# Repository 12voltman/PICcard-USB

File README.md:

# PICcard-USB
Small PIC development board for high resistive switching (à-la Makey Makey)

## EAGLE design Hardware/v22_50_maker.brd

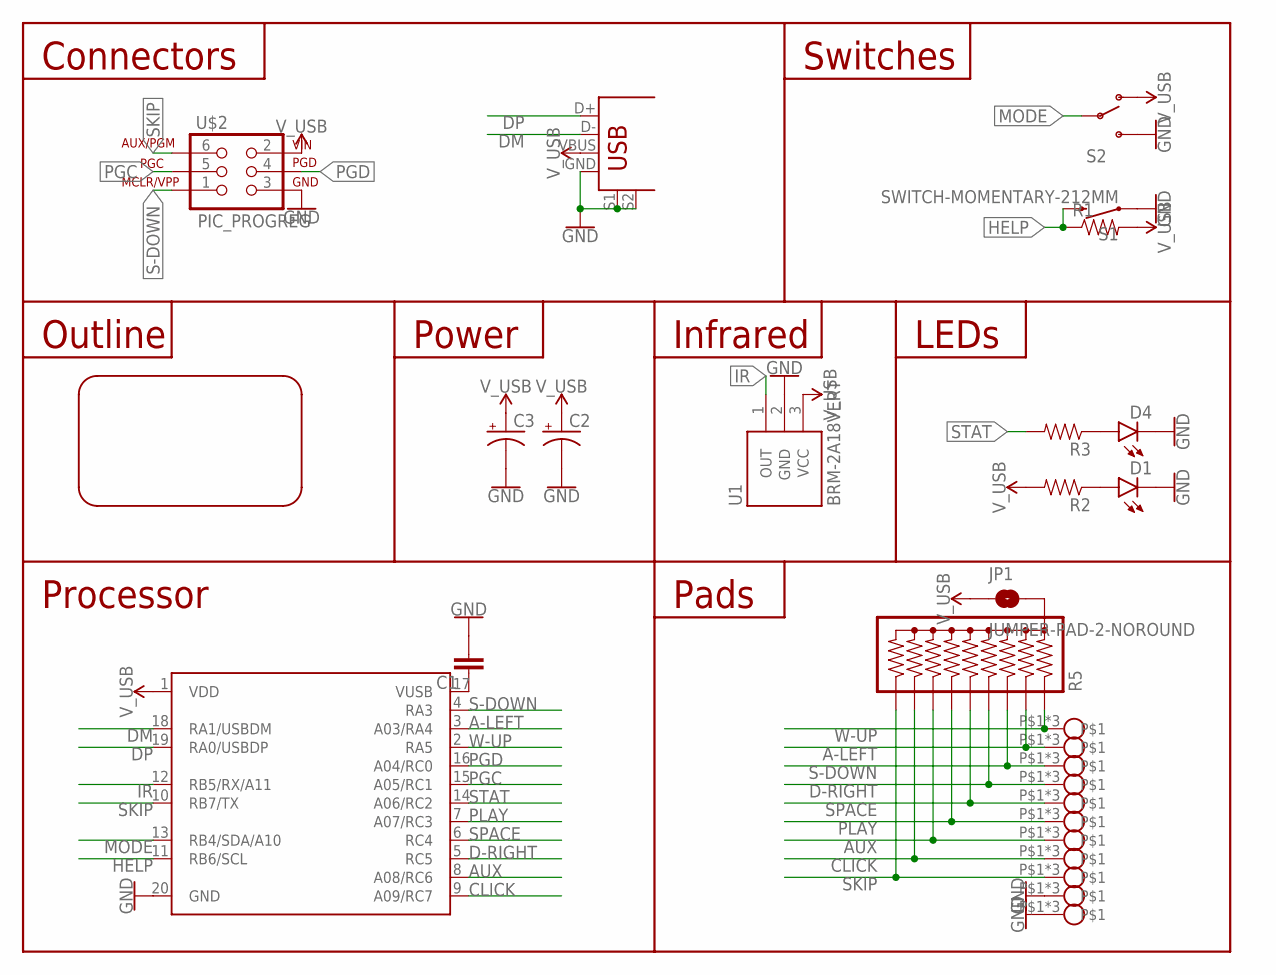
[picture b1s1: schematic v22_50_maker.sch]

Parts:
C1: CAPPTH; CAP-PTH-SMALL
C2: CAP_POLPTH2; CPOL-RADIAL-10UF-25V
C3: CAP_POLPTH1; CPOL-RADIAL-100UF-25V
D1, D4: LED3MM
JP1: JUMPER-PAD-2-NOROUND; PAD-JUMPER-2-NO_YES_SILK_ROUND
R1, R2, R3: RESISTORAXIAL-0.3; AXIAL-0.3
R5: RPACK-BUSSED-9ROUND; RPACK-SIP-PTH-9
S1: SWITCH-MOMENTARY-212MM; TACTILE-PTH-12MM
S2: SWITCH-SPDTPTH; SWITCH-SPDT
U1: BRM-2A18VERT; BRM-2508_VERT
U$1: PIC16F1459-I/MLDIL; DIL20
U$2: PIC_PROGREG; 1X06
U$3: USB+SHIELD; USB-B-PTH
U$4, U$5, U$6, U$7, U$8, U$9, U$10, U$11, U$12, U$13, U$14: ALLIGATOR; ALLIGATOR_CLIP_CONNECTOR
U$15: CARD_STANDARD50MM; IEC-7810_ID-1_50MM

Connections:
A-LEFT: R5.P$3 (3), U$1.3 (A03/RA4), U$4.P$1, U$4.P$2, U$4.P$3
AUX: R5.P$8 (8), U$1.8 (A08/RC6), U$10.P$1, U$10.P$2, U$10.P$3
CLICK: R5.P$9 (9), U$1.9 (A09/RC7), U$11.P$1, U$11.P$2, U$11.P$3
D-RIGHT: R5.P$5 (5), U$1.5 (RC5), U$5.P$1, U$5.P$2, U$5.P$3
DM: U$1.18 (RA1/USBDM), U$3.D-
DP: U$1.19 (RA0/USBDP), U$3.D+
GND: C1.2, C2.2 (-), C3.2 (-), D1.K (C), D4.K (C), S1.1, S1.2 (1), S2.3 (S), U1.2 (GND), U$1.20 (GND), U$2.3 (GND), U$3.GND, U$3.S1, U$3.S2, U$13.P$1, U$13.P$2, U$13.P$3, U$14.P$1, U$14.P$2, U$14.P$3
HELP: R1.P$1 (1), S1.3 (2), S1.4 (2), U$1.11 (RB6/SCL)
IR: U1.1 (OUT), U$1.12 (RB5/RX/A11)
MODE: S2.2, U$1.13 (RB4/SDA/A10)
unnamed: D4.A, R3.P$1 (1)
unnamed: C1.1, U$1.17 (VUSB)
unnamed: JP1.2, R5.P$1 (1)
unnamed: D1.A, R2.P$1 (1)
PGC: U$1.15 (A05/RC1), U$2.5 (PGC)
PGD: U$1.16 (A04/RC0), U$2.4 (PGD)
PLAY: R5.P$7 (7), U$1.7 (A07/RC3), U$9.P$1, U$9.P$2, U$9.P$3
S-DOWN: R5.P$4 (4), U$1.4 (RA3), U$2.1 (MCLR/VPP), U$7.P$1, U$7.P$2, U$7.P$3
SKIP: R5.P$10 (10), U$1.10 (RB7/TX), U$2.6 (AUX/PGM), U$12.P$1, U$12.P$2, U$12.P$3
SPACE: R5.P$6 (6), U$1.6 (RC4), U$8.P$1, U$8.P$2, U$8.P$3
STAT: R3.P$2 (2), U$1.14 (A06/RC2)
V_USB: C2.1 (+), C3.1 (+), JP1.1, R1.P$2 (2), R2.P$2 (2), S2.1 (O), U1.3 (VCC), U$1.1 (VDD), U$2.2 (VIN), U$3.VBUS
W-UP: R5.P$2 (2), U$1.2 (RA5), U$6.P$1, U$6.P$2, U$6.P$3

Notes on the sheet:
Switches
Connectors
Outline
Power
Infrared
LEDs
Pads
Processor

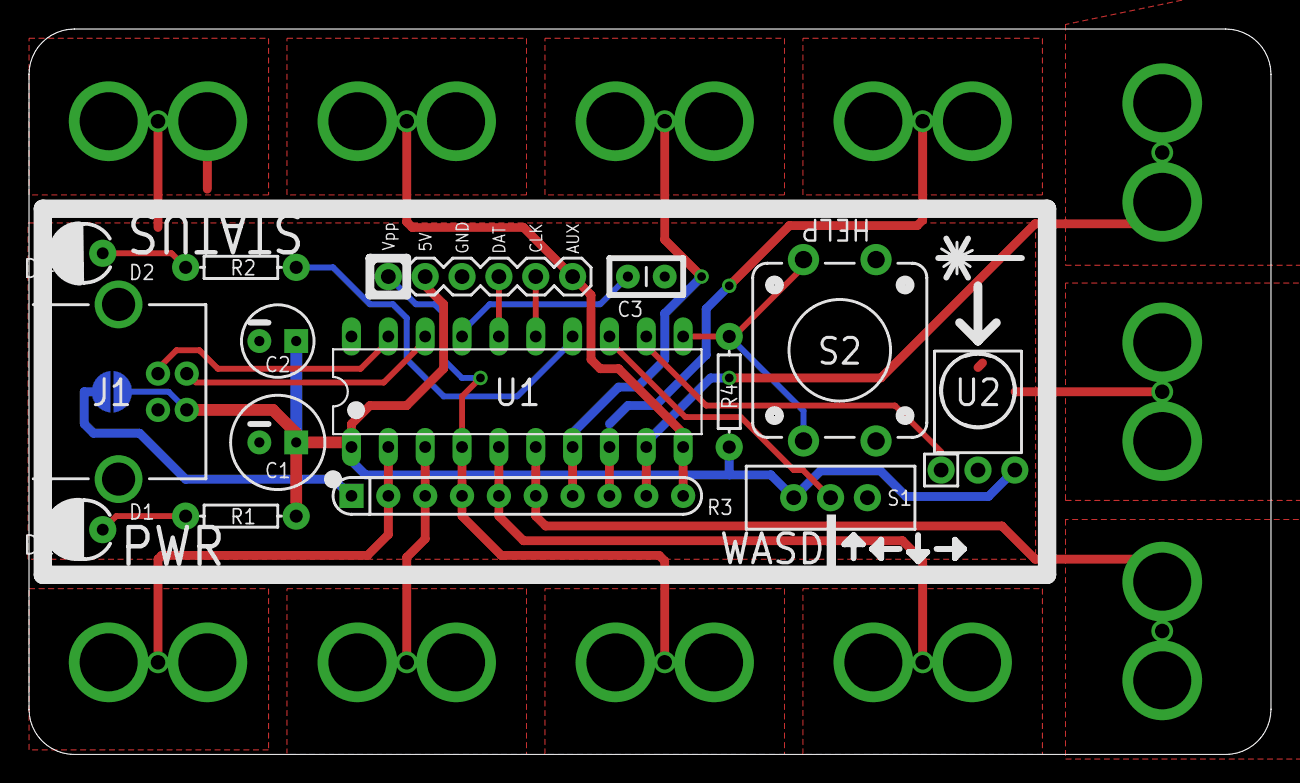
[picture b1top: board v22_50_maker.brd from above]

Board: 2 copper layers, 85.6 x 50.0 mm, 28 parts (1 on the bottom side), 23 nets.

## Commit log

2018-05-16 Added hardware folder
    Added EAGLE schematic and board files for single 50mm board with Rose-Hulman Makerlab branding. Also includes images of schematics and boards for quick reference without having to open EAGLE.
2021-09-18 Initial Bill of Materials List

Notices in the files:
parts and their libraries:
SparkFun-Connectors: Licensing: Creative Commons ShareAlike 4.0 International - https://creativecommons.org/licenses/by-sa/4.0
